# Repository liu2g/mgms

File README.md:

# Modular Garden Monitoring System
Senior Capstone Design Project

*EECS Department, CEAS College, University of Cincinnati*

**Team CE12**
- Sadie Gladden (gladdesm@mail.uc.edu)
- Alan Trester (tresteat@mail.uc.edu)
- Liu / Zuguang Liu (liu2z2@mail.uc.edu)
- Eric Krenz (krenzew@mail.uc.edu)
- Technical advisor: Dr. Zachariah Fuchs (fuchsze@ucmail.uc.edu)
- Academic instructor: Dr. Carla Purdy (purdycc@ucmail.uc.edu)

## Project Description
The MGMS is an IoT solution to help homeowners, garden enthusiasts, and farmers care for their lawns and gardens in a more informed and effective way while also reducing wasteful water usage.

Our proposed solution is a modular design consisting of a central hub which will wirelessly connect to multiple sensing and watering modules that can be placed around a garden or house.
The hub hosts the central user interface and allow for customizing different garden setups.
The hub software will make decisions based on the user configuration to control connected field modules in order to continuously monitor and water the garden.
The user interface will be able to alert the user to garden events and make suggestions based on information available on the internet.
The most important feature of the system should be modularity in freedom to interface a variety of system components in many different configurations.

System Control Scheme | System Network Topology
:---: | :---:
 | 

Being a self-proposed project, this proof-of-concept system was designed over the 2020 - 2021 academic year to fulfill the team's senior design requirement.
At the end, we were able to deliver part of the implementation, including the sensor module [hardware design](design/sensor-module/) and its [firmware](src/cpp-sensor-module/), as well as the [user application](src/python-gui/) at the front end.

For detailed information, see our [virtual poster site](https://mgmsteam12.weebly.com/) and related [documents](docs).

## Directory Structure
    .
    ├── design                      # Hardware design root dir
    │   └── sensor-module           # design files for sensor module
    ├── src                         # Software source root dir
    |   ├── cpp-sensor-module       # sensor module firmware
    |   ├── python-gui              # frontend application
    |   └── make-avr-template       # makefile template for avr-gcc
    └── docs

## License
This project is licensed under the [MIT License](LICENSE).

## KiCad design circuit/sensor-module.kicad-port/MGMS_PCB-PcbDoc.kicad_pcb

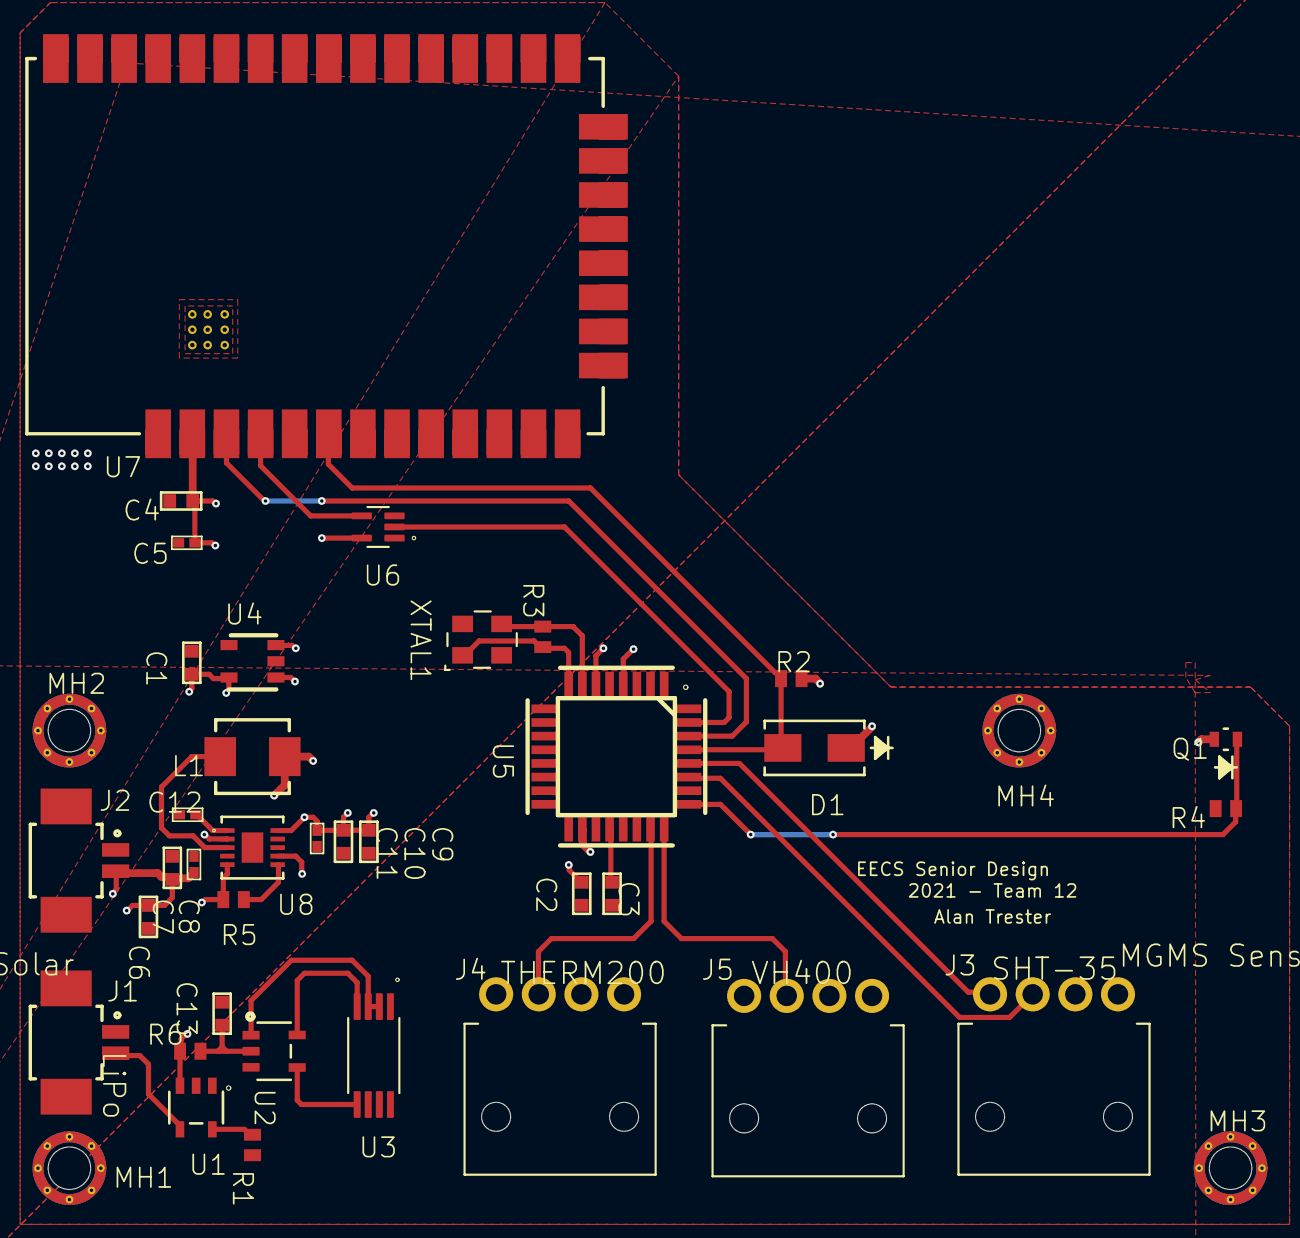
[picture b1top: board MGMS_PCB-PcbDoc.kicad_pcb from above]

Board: 2 copper layers, 40 parts (0 on the bottom side), 25 nets.

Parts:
C1, C10: CAP, 1.0uF, 50V, 10%, X7R, 0603(1608M); CAP0603_HD
C2, C3, C6, C13: CAP, 100nF, 100V, 10%, X7R, 0603(1608M); CAP0603_HD
C4, C7, C9: CAP, 10uF, 10V, 15%, X5R, 0603(1608M); CAP0603_HD
C5, C8, C11, C12: CAP, 0.1uF, 25V, 10%, X7R, 0402(1005M); CAP0402_HD
D1: SMA_DIODE
J1, J2: 2 Pos Molex Microblade; MOLEX_53261-0271
J3, J4, J5: Connector, 2.5MM, 4 pos Singlel Row Header - Righ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; CON_105313-2304
L1: Inductor SMT, 27nH, Wire-wound Ceramic, 0402HP; IND_1616
MH1, MH2, MH3, MH4: Mounting Hole, 2-56 Pan Head, Close Fit Hole; MH_2-56_PH
Q1: ALS-PT19 PHOTOTRANSISTOR
R1, R2, R3, R4, R5, R6: RES_0603_HD
U1: 800mA Standalone linear Li-ion charger with therm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; TSOT-23-5
U2: Battery Protection IC for LiPo; SOT-25
U3: 8-TSSOP
U4: Arduino 3.3v regulator; SOT23-5
U5: Arduino ATMEGA328 Chip; 32A_ATM
U6: Single Bus 3-State Buffer; SOT-SC70-5
U7: XBEE_1W_BASE
U8: Used on Pololu step up regulator board; 10-VFDFN Exposed Pad
XTAL1: 16MHz Oscillator; OSC SMD-4

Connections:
3V3: C1.1, C4.1, C5.1, U4.5, U6.5, U7.2
+5: C2.1, C9.1, C10.1, C11.1, D1.1, J3.2, J4.2, J5.2, Q1.2, R2.1, U5.4, U5.6, U5.18, U8.2, U8.10
GND: C1.2, C2.2, C3.2, C4.2, C5.2, C6.2, C7.2, C8.2, C9.2, C10.2, C11.2, C12.2, C13.2, J1.1, J1.P1, J1.P2, J2.1, J2.P1, J2.P2, J3.1, J4.1, J5.1, MH1.1, MH2.1, MH3.1, MH4.1, R1.2, R4.1, U1.2, U2.3, U3.6, U3.7, U4.2, U5.3, U5.5, U5.21, U6.1, U6.3, U7.1, U7.11, U7.13, U7.22, U7.35, U7.38, U8.4, U8.8, U8.9, U8.11, XTAL1.2, XTAL1.4
NetC3_1: C3.1, U5.20
NetC12_1: C12.1, U8.1
NetC13_1: C13.1, R6.2, U2.2
NetD1_2: D1.2, R2.2, U5.29, U7.6
NetJ2_2: J2.2, U1.4
NetJ3_3: J3.3, U5.27
NetJ3_4: J3.4, U5.28
NetJ4_3: J4.3, U5.23
NetJ5_3: J5.3, U5.24
NetL1_2: L1.2, U8.3
NetQ1_1: Q1.1, R4.2, U5.25
NetR1_1: R1.1, U1.5
NetR3_1: R3.1, U5.8, XTAL1.1
NetR3_2: R3.2, U5.7, XTAL1.3
NetR5_2: R5.2, U8.6
NetU2_1: U2.1, U3.2, U3.3
NetU2_4: U2.4, U3.5
NetU2_5: U2.5, U3.4
NetU5_30: U5.30, U7.3
NetU5_31: U5.31, U6.2
NetU6_4: U6.4, U7.4
V_in: C6.1, C7.1, C8.1, J1.2, L1.1, R5.1, R6.1, U1.3, U4.1, U4.3, U8.5, U8.7

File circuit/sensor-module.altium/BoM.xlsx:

Comment | Description | Designator | Footprint | LibRef | Quantity | Supplier Unit Price 1 | Supplier 1
CAP_1.0uF_50V_10%_X7R_0603(1608M) | CAP, 1.0uF, 50V, 10%, X7R, 0603(1608M) | C1, C10 | CAP0603_HD | CAP_1.0uF_50V_10%_X7R_0603(1608M) | 2 | 0.28999999999999998 | Digi-Key | 0.57999999999999996
CAP_100nF_100V_10%_X7R_0603(1608M) | CAP, 100nF, 100V, 10%, X7R, 0603(1608M) | C2, C3, C6, C13 | CAP0603_HD | CAP_100nF_100V_10%_X7R_0603(1608M) | 4 |  |  | 0
CAP_10uF_10V_15%_X5R_0603(1608M) | CAP, 10uF, 10V, 15%, X5R, 0603(1608M) | C4, C7, C9 | CAP0603_HD | CAP_10uF_10V_15%_X5R_0603(1608M) | 3 |  | Digi-Key | 0
CAP_0.1uF_25V_10%_X7R_0402(1005M) | CAP, 0.1uF, 25V, 10%, X7R, 0402(1005M) | C5, C8, C11, C12 | CAP0402_HD | CAP_0.1uF_25V_10%_X7R_0402(1005M) | 4 |  | Digi-Key | 0
Diode_S1B-13-F |  | D1 | SMA_DIODE | Diode_S1B-13-F | 1 | 0.25 | Digi-Key | 0.25
0532610271 | 2 Pos Molex Microblade | J1, J2 | MOLEX_53261-0271 | 0532610271 | 2 | 0.47 | Digi-Key | 0.94
CON_105313-2304 | Connector, 2.5MM, 4 pos Singlel Row Header - Right Angle | J3, J4, J5 | CON_105313-2304 | CON_105313-2304 | 3 |  |  | 0
IND_2.2uH_WireWound | Inductor SMT, 27nH, Wire-wound Ceramic, 0402HP | L1 | IND_1616 | IND_2.2uH_WireWound | 1 | 1.1299999999999999 | Mouser | 1.1299999999999999
ALS-PT19 Phototransistor |  | Q1 | ALS-PT19 Phototransistor | ALS-PT19 Phototransistor | 1 | 0.33 | Digi-Key | 0.33
RES_1.2K_0.1%_0.1W_0603 |  | R1 | RES_0603_HD | RES_1.2K_0.1%_0.1W_0603 | 1 | 0.31 | Digi-Key | 0.31
RES_10.0K_1%_0.33W_0603 |  | R2, R4 | RES_0603_HD | RES_10.0K_1%_0.33W_0603 | 2 | 0.17 | Digi-Key | 0.34
RES_1.00M_0.1%_0.1W_0603 |  | R3 | RES_0603_HD | RES_1.00M_0.1%_0.1W_0603 | 1 | 0.3 | Digi-Key | 0.3
RES_100K_0.1%_0.1W_0603 |  | R5 | RES_0603_HD | RES_100K_0.1%_0.1W_0603 | 1 | 0.1 | Digi-Key | 0.1
100R |  | R6 | RES_0603_HD | RES_100_0.5%_1/16W_0603 | 1 | 0.1 | Digi-Key | 0.1
STC4054GR | 800mA Standalone linear Li-ion charger with thermal regulation | U1 | TSOT-23-5 | STC4054GR | 1 | 1.58 | Digi-Key | 1.58
AP9101CAK-ABTRG1 | Battery Protection IC for LiPo | U2 | SOT-25 | AP9101CAK-ABTRG1 | 1 | 0.46 | Digi-Key | 0.46
TSM6968DCA |  | U3 | 8-TSSOP | TSM6968DCA | 1 | 0.97 | Digi-Key | 0.97
LP298533DBVR Voltage Regulator | Arduino 3.3v regulator | U4 | SOT23-5 | LP298533DBVR Voltage Regulator | 1 | 0.53 | Digi-Key | 0.53
ATMEGA328P_SMD | Arduino ATMEGA328 Chip | U5 | 32A_ATM | ATMEGA328P_SMD | 1 | 2.4 | Digi-Key | 2.4
SN74LVC1G125DCKR | Single Bus 3-State Buffer | U6 | SOT-SC70-5 | SN74LVC1G125DCKR | 1 | 0.32 | Digi-Key | 0.32
XBEE 3 SMD |  | U7 | XBee_1W_Base | XBEE 3 SMD | 1 | 16.21 | Digi-Key | 16.21
TPS61200DR Voltage Boost Regulator | Used on Pololu step up regulator board | U8 | 10-VFDFN Exposed Pad | TPS61200DR Voltage Boost Regulator | 1 | 2.89 | Digi-Key | 2.89
CX3225SB16000D0GZJC1 | 16MHz Oscillator | XTAL1 | OSC SMD-4 | CX3225SB16000D0GZJC1 | 1 | 0.6 | Digi-Key | 0.6
 |  |  |  |  |  |  |  | 30.340000000000003

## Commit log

2020-09-01 added documents
2020-09-01 update slides
2020-09-01 gitignore for docs
2020-09-01 Updated Slide Deck Tex File
2020-09-01 remove ignored files
2020-09-01 render slides
2020-09-01 update docs
2020-09-01 Adding personal tasks to documtent
2020-09-01 final push on docs
2020-09-01 small tweaks for slide
2020-09-02 update dhf and readme
2020-09-02 add branding for uc in slide
2020-09-02 update dhf
2020-09-08 renamed doc
2020-09-08 Adding lecture files to determine similarities for weekly tasks
2020-09-08 Update README.md
    Updated with location of DHF
2020-09-08 Add Canvas files for Kosel section
2020-09-09 adding completed Team effectiveness survey
2020-09-09 Update/Fix DHF Contents order
2020-09-09 prelim prelim proposal pdf in docs class-assignments
2020-09-09 i messed up lius name cuz i dumb dumb
2020-09-09 fixed contents numbering
2020-09-09 elevator pitch draft one
2020-09-09 Added some stuff to prelim proposal
2020-09-09 update elevator pitch
2020-09-09 add pdf to ignore
2020-09-09 update gitignore
2020-09-09 update gitignore the third time
2020-09-10 update readme warning
2020-09-10 reindexes files in DHF
2020-09-11 implement Gantt chart on DHF
2020-09-11 transfer prelim proposal to separate folder
2020-09-11 update prelim proposal
2020-09-11 import prelim proposal info into DHF
2020-09-11 Updated elevator pitch
2020-09-11 released bbl
2020-09-11 dumb ass commas
2020-09-11 Did the ol' fox news to the problem statement
2020-09-11 Fixed it
2020-09-11 Final updates to prelim proposal
2020-09-12 redid title page - fixed wording and made lists prettier
2020-09-12 Updated problem statement and fixed section headers
2020-09-12 Made lists better, added infor about myself
2020-09-12 New file
2020-09-12 it worked for me
2020-09-22 update gentt chart
2020-09-22 add Eric to dhf
2020-09-22 Adding sadie things
2020-09-22 new guy new bio
2020-09-27 update overleaf link
2020-11-14 added initial code and template for C
2020-11-16 avr support for windows
2020-11-16 some changes
2020-11-16 update makefile
2020-11-16 fix readme
2021-01-19 update for the template
2021-03-14 Update SHT35 code
2021-03-15 Working SHT35
2021-03-18 update SHT sensor code
2021-03-18 update main sensor module code
2021-03-18 reformat README
2021-03-18 Adding python file and action list
2021-03-18 gui stuff
2021-03-22 Messing with Gui and scanning working on parsing collected data and graphs next
2021-03-23 GUI updates - should remove clear button just for testing purposes
2021-03-23 Set sampling frequencyinput
2021-03-23 Threading Working I think like 90% sure
2021-03-24 Auto Collection From Radios Does Stuff and Things
2021-03-24 data dummy stuff for graphs
2021-03-24 cool graphs and gui
2021-05-13 Refactor some directories and names
2021-05-13 Additional refactor
2021-05-13 Refactor avr-gcc template
2021-05-13 Clean C++ code
2021-05-13 Refactor python code
2021-05-13 Reformat contact info in C++
2021-05-13 Clean up python code
2021-05-14 - Add small detail to python code and README - Remove IDE settings (PyCharm and VSCoce)
2021-05-14 - Add main TODO - Pull gitignore to root
2021-05-14 Add PCB projects in Altium and KiCAD
2021-05-15 Update part of README
2021-05-15 Reformat README and refactor some dir
2021-05-15 Refactor `circuit` dir name
2021-05-15 Refactor `circuit` subdir
2021-05-15 Document circuit
2021-05-15 Update TODO
2021-05-15 Revamp docs
2021-05-15 Add design proposal and design plan doc
2021-05-15 Refactor dirs
2021-05-15 Add all latex docs
2021-05-15 Remove vscode dir
2021-05-15 Small detail to C++ readme
2021-05-16 Update root readme
2021-05-16 Complete root readme and update license
2021-05-16 Update license
2021-05-16 Resize poster img
